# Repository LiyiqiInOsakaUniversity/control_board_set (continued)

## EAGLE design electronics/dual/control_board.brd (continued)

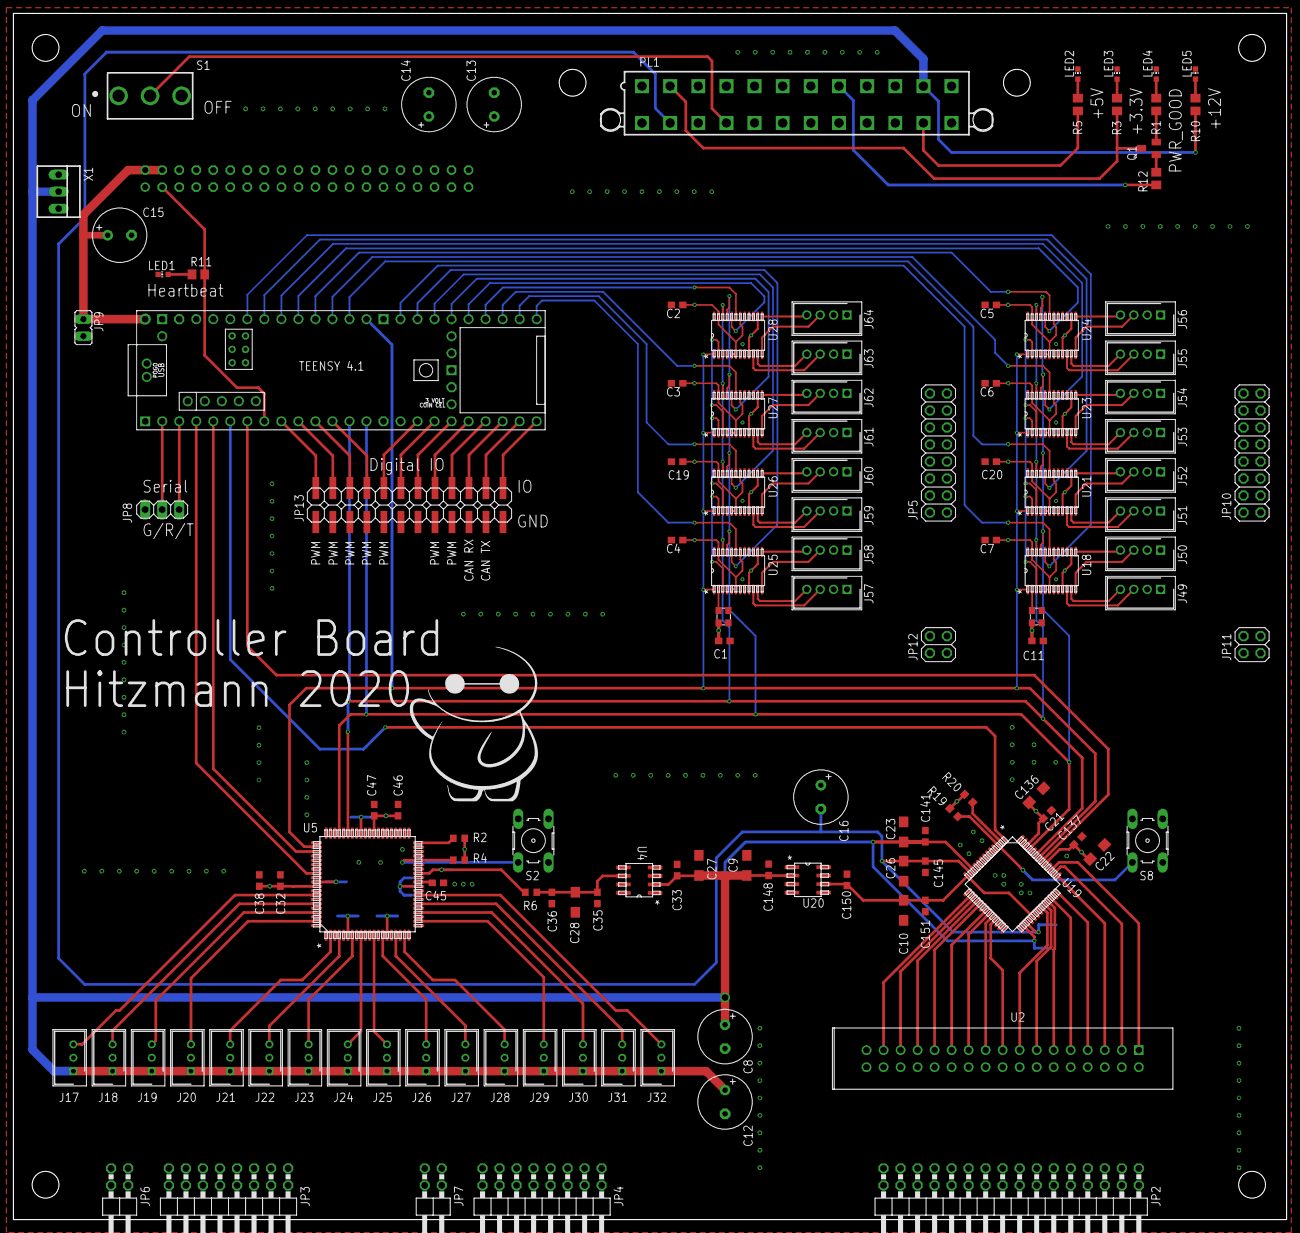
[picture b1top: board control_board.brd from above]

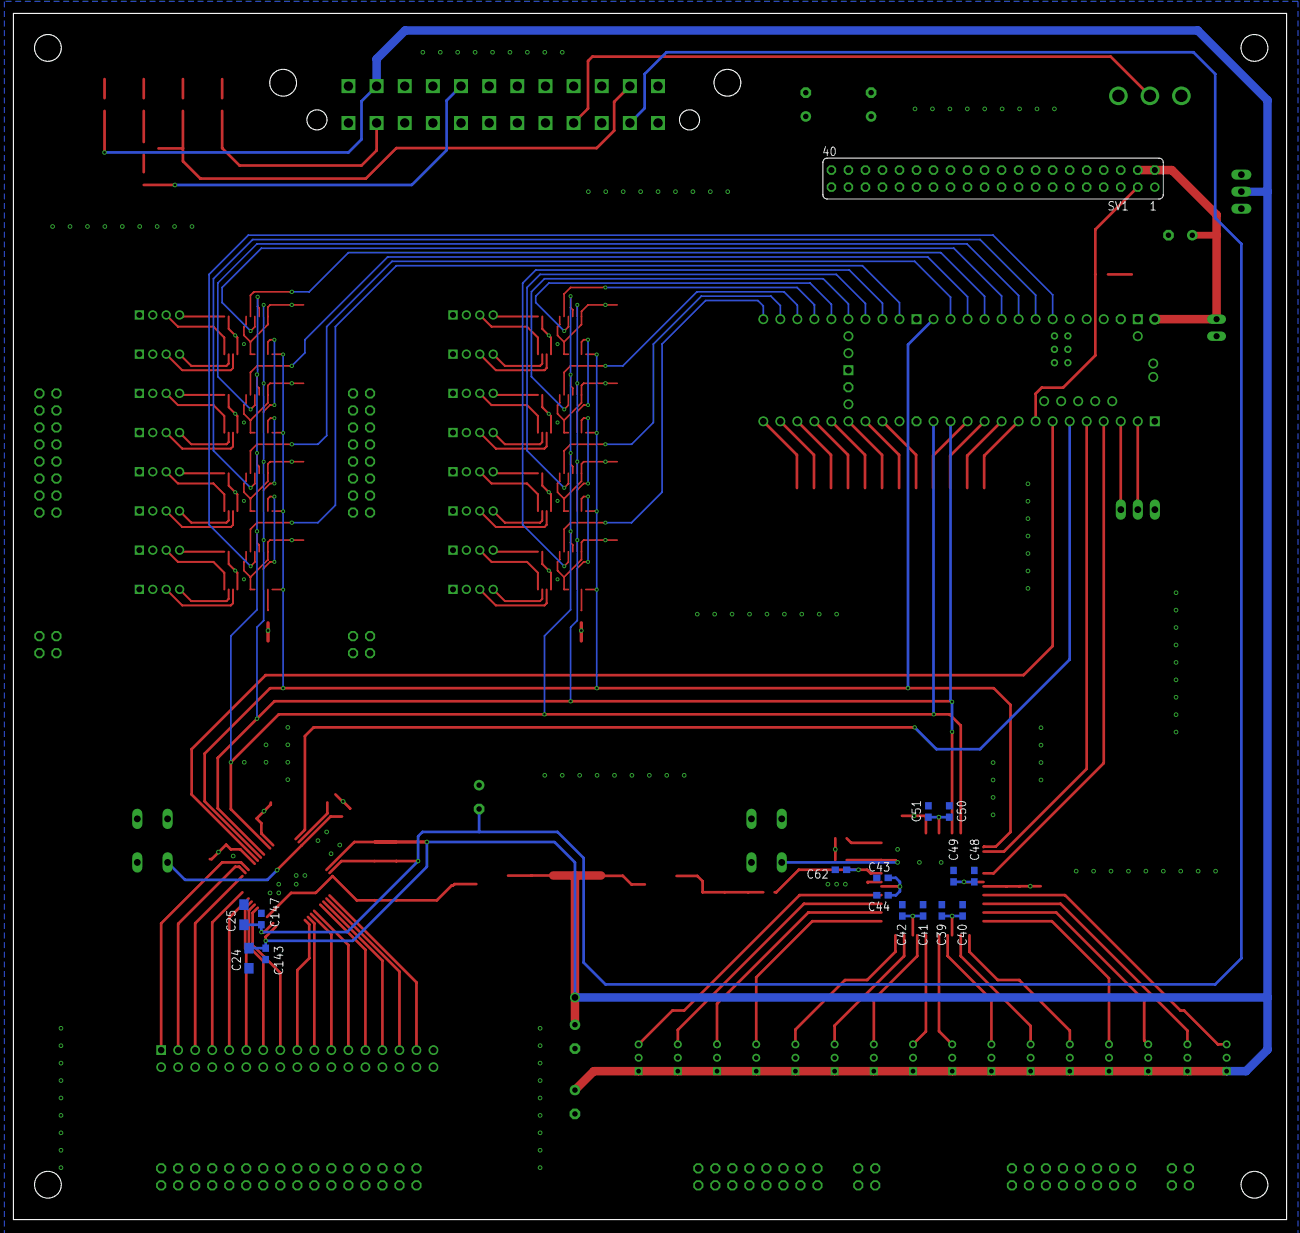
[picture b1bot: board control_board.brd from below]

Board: 4 copper layers, 190.0 x 180.0 mm, 137 parts (16 on the bottom side), 135 nets.

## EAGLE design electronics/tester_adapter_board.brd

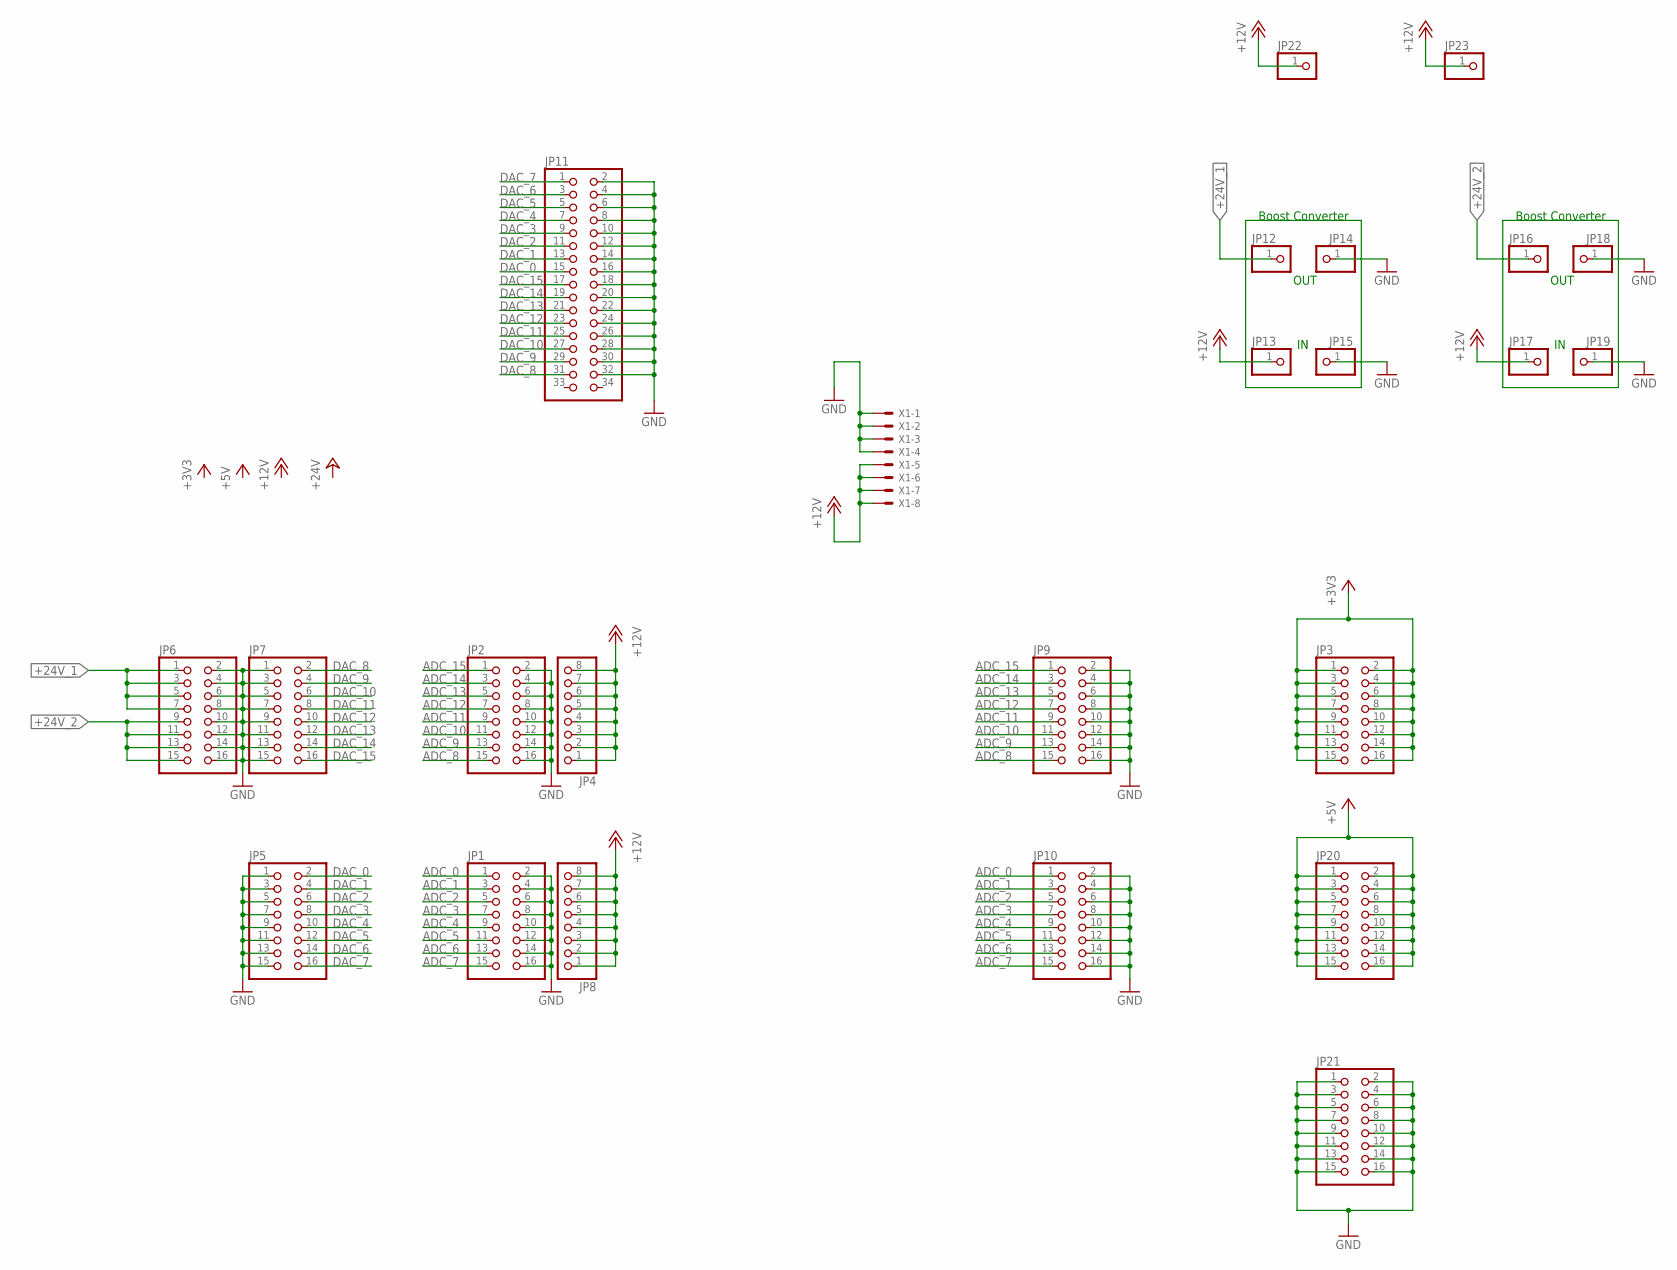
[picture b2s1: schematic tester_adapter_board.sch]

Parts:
JP1, JP2, JP3, JP5, JP6, JP7, JP9, JP10, JP20, JP21: PINHD-2X8; 2X08
JP4, JP8: PINHD-1X08_2.54-S; 1X08-S
JP11: PINHD-2X17; 2X17
JP12, JP13, JP16, JP17: PINHD-1X01_2.54; 1X01
JP14, JP15, JP18, JP19: PINHD-1X01_2.54-S; 1X01-S
JP22, JP23: PINHD-1X01_2.54-SMD; 1X01SMD
X1: 5566-8

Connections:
+3V3: JP3.1, JP3.2, JP3.3, JP3.4, JP3.5, JP3.6, JP3.7, JP3.8, JP3.9, JP3.10, JP3.11, JP3.12, JP3.13, JP3.14, JP3.15, JP3.16
+5V: JP20.1, JP20.2, JP20.3, JP20.4, JP20.5, JP20.6, JP20.7, JP20.8, JP20.9, JP20.10, JP20.11, JP20.12, JP20.13, JP20.14, JP20.15, JP20.16
+12V: JP4.1, JP4.2, JP4.3, JP4.4, JP4.5, JP4.6, JP4.7, JP4.8, JP8.1, JP8.2, JP8.3, JP8.4, JP8.5, JP8.6, JP8.7, JP8.8, JP13.1, JP17.1, JP22.1, JP23.1, X1.5, X1.6, X1.7, X1.8
+24V_1: JP6.1, JP6.3, JP6.5, JP6.7, JP12.1
+24V_2: JP6.9, JP6.11, JP6.13, JP6.15, JP16.1
ADC_0: JP1.1, JP10.1
ADC_1: JP1.3, JP10.3
ADC_2: JP1.5, JP10.5
ADC_3: JP1.7, JP10.7
ADC_4: JP1.9, JP10.9
ADC_5: JP1.11, JP10.11
ADC_6: JP1.13, JP10.13
ADC_7: JP1.15, JP10.15
ADC_8: JP2.15, JP9.15
ADC_9: JP2.13, JP9.13
ADC_10: JP2.11, JP9.11
ADC_11: JP2.9, JP9.9
ADC_12: JP2.7, JP9.7
ADC_13: JP2.5, JP9.5
ADC_14: JP2.3, JP9.3
ADC_15: JP2.1, JP9.1
DAC_0: JP5.2, JP11.15
DAC_1: JP5.4, JP11.13
DAC_2: JP5.6, JP11.11
DAC_3: JP5.8, JP11.9
DAC_4: JP5.10, JP11.7
DAC_5: JP5.12, JP11.5
DAC_6: JP5.14, JP11.3
DAC_7: JP5.16, JP11.1
DAC_8: JP7.2, JP11.31
DAC_9: JP7.4, JP11.29
DAC_10: JP7.6, JP11.27
DAC_11: JP7.8, JP11.25
DAC_12: JP7.10, JP11.23
DAC_13: JP7.12, JP11.21
DAC_14: JP7.14, JP11.19
DAC_15: JP7.16, JP11.17
GND: JP1.2, JP1.4, JP1.6, JP1.8, JP1.10, JP1.12, JP1.14, JP1.16, JP2.2, JP2.4, JP2.6, JP2.8, JP2.10, JP2.12, JP2.14, JP2.16, JP5.1, JP5.3, JP5.5, JP5.7, JP5.9, JP5.11, JP5.13, JP5.15, JP6.2, JP6.4, JP6.6, JP6.8, JP6.10, JP6.12, JP6.14, JP6.16, JP7.1, JP7.3, JP7.5, JP7.7, JP7.9, JP7.11, JP7.13, JP7.15, JP9.2, JP9.4, JP9.6, JP9.8, JP9.10, JP9.12, JP9.14, JP9.16, JP10.2, JP10.4, JP10.6, JP10.8, JP10.10, JP10.12, JP10.14, JP10.16, JP11.2, JP11.4, JP11.6, JP11.8, JP11.10, JP11.12, JP11.14, JP11.16, JP11.18, JP11.20, JP11.22, JP11.24, JP11.26, JP11.28, JP11.30, JP11.32, JP14.1, JP15.1, JP18.1, JP19.1, JP21.1, JP21.2, JP21.3, JP21.4, JP21.5, JP21.6, JP21.7, JP21.8, JP21.9, JP21.10, JP21.11, JP21.12, JP21.13, JP21.14, JP21.15, JP21.16, X1.1, X1.2, X1.3, X1.4

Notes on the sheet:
Boost Converter
OUT

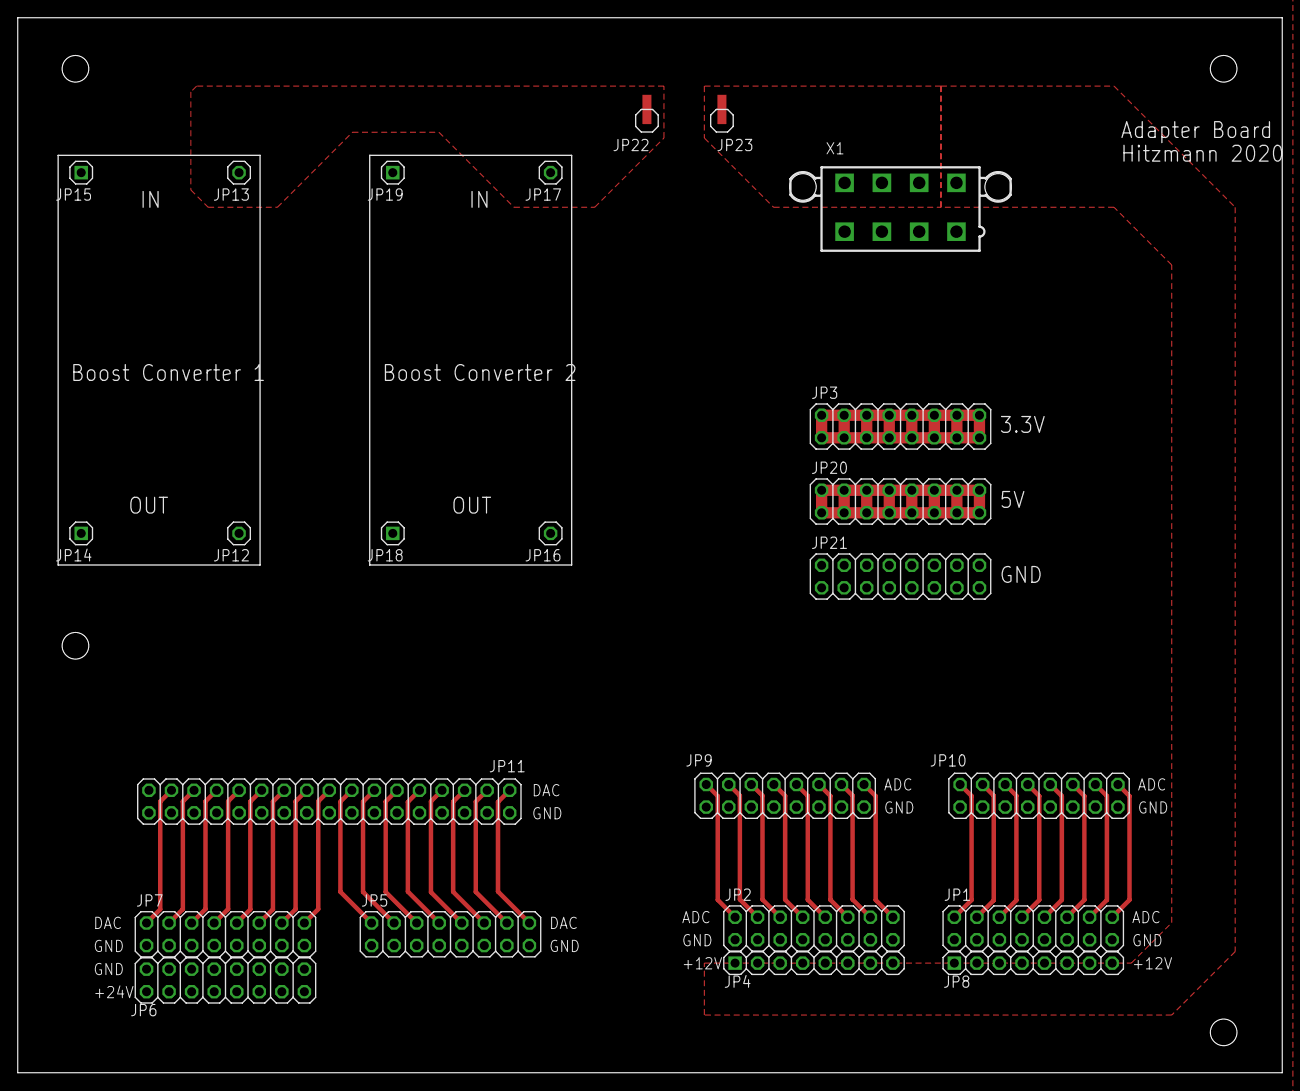
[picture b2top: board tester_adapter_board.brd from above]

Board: 2 copper layers, 142.4 x 118.8 mm, 24 parts (0 on the bottom side), 38 nets.

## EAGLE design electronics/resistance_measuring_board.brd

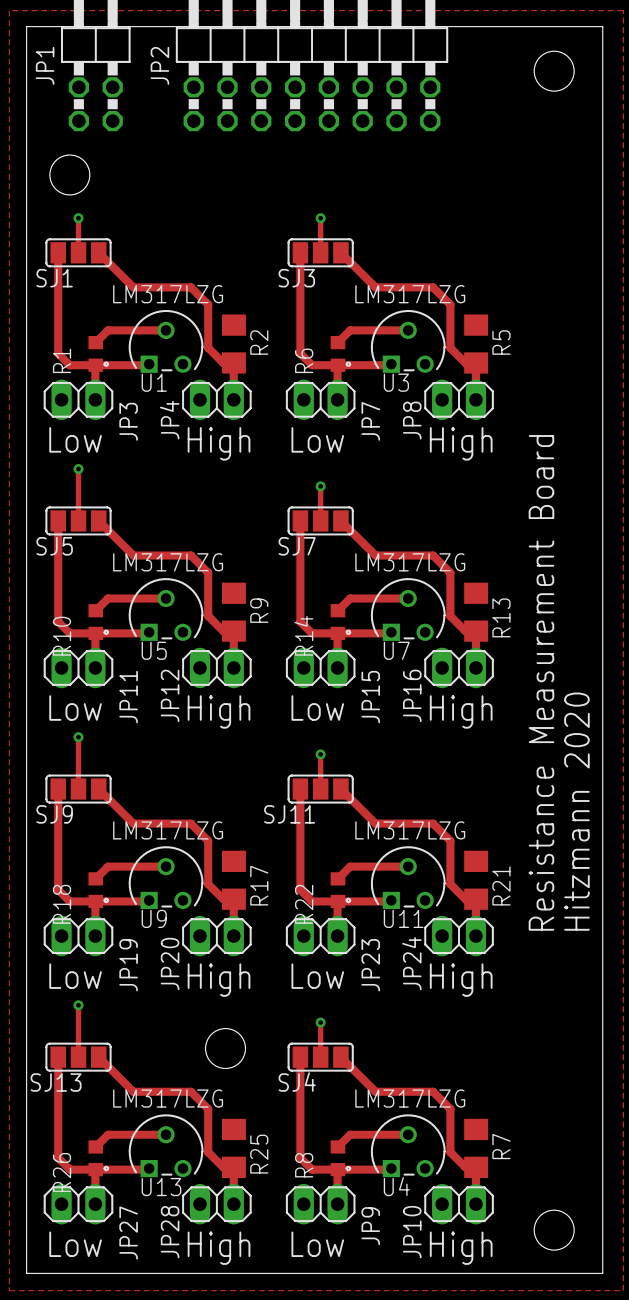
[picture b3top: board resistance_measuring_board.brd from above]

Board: 4 copper layers, 43.3 x 93.7 mm, 50 parts (0 on the bottom side), 34 nets.

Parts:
JP1: 2X02/90
JP2: 2X08/90
JP3, JP4, JP7, JP8, JP9, JP10, JP11, JP12, JP15, JP16, JP19, JP20, JP23, JP24, JP27, JP28: 1X02
R1, R6, R8, R10, R14, R18, R22, R26: 12R, 0.1%; R0603
R2, R5, R7, R9, R13, R17, R21, R25: 1K, 0.1%; R1206
SJ1, SJ3, SJ4, SJ5, SJ7, SJ9, SJ11, SJ13: SJ_2
U1, U3, U4, U5, U7, U9, U11, U13: LM317LZG; TO-92_ONS

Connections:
GND: JP2.2, JP2.4, JP2.6, JP2.8, JP2.10, JP2.12, JP2.14, JP2.16, JP3.2, JP7.2, JP9.2, JP11.2, JP15.2, JP19.2, JP23.2, JP27.2, R2.1, R5.1, R7.1, R9.1, R13.1, R17.1, R21.1, R25.1
unnamed: R6.1, U3.2
unnamed: R8.1, U4.2
unnamed: R10.1, U5.2
unnamed: R14.1, U7.2
unnamed: R18.1, U9.2
unnamed: R22.1, U11.2
unnamed: R26.1, U13.2
unnamed: R1.1, U1.2
SENSE_1: JP2.1, SJ1.2
SENSE_2: JP2.3, SJ3.2
SENSE_3: JP2.5, SJ5.2
SENSE_4: JP2.7, SJ7.2
SENSE_5: JP2.9, SJ9.2
SENSE_6: JP2.11, SJ11.2
SENSE_7: JP2.13, SJ13.2
SENSE_8: JP2.15, SJ4.2
SENSE_HI_1: JP4.2, R2.2, SJ1.1
SENSE_HI_2: JP8.2, R5.2, SJ3.1
SENSE_HI_3: JP12.2, R9.2, SJ5.1
SENSE_HI_4: JP16.2, R13.2, SJ7.1
SENSE_HI_5: JP20.2, R17.2, SJ9.1
SENSE_HI_6: JP24.2, R21.2, SJ11.1
SENSE_HI_7: JP28.2, R25.2, SJ13.1
SENSE_HI_8: JP10.2, R7.2, SJ4.1
SENSE_LO_1: JP3.1, R1.2, SJ1.3, U1.1
SENSE_LO_2: JP7.1, R6.2, SJ3.3, U3.1
SENSE_LO_3: JP11.1, R10.2, SJ5.3, U5.1
SENSE_LO_4: JP15.1, R14.2, SJ7.3, U7.1
SENSE_LO_5: JP19.1, R18.2, SJ9.3, U9.1
SENSE_LO_6: JP23.1, R22.2, SJ11.3, U11.1
SENSE_LO_7: JP27.1, R26.2, SJ13.3, U13.1
SENSE_LO_8: JP9.1, R8.2, SJ4.3, U4.1
VCC: JP1.1, JP1.2, JP1.3, JP1.4, JP4.1, JP8.1, JP10.1, JP12.1, JP16.1, JP20.1, JP24.1, JP28.1, U1.3, U3.3, U4.3, U5.3, U7.3, U9.3, U11.3, U13.3

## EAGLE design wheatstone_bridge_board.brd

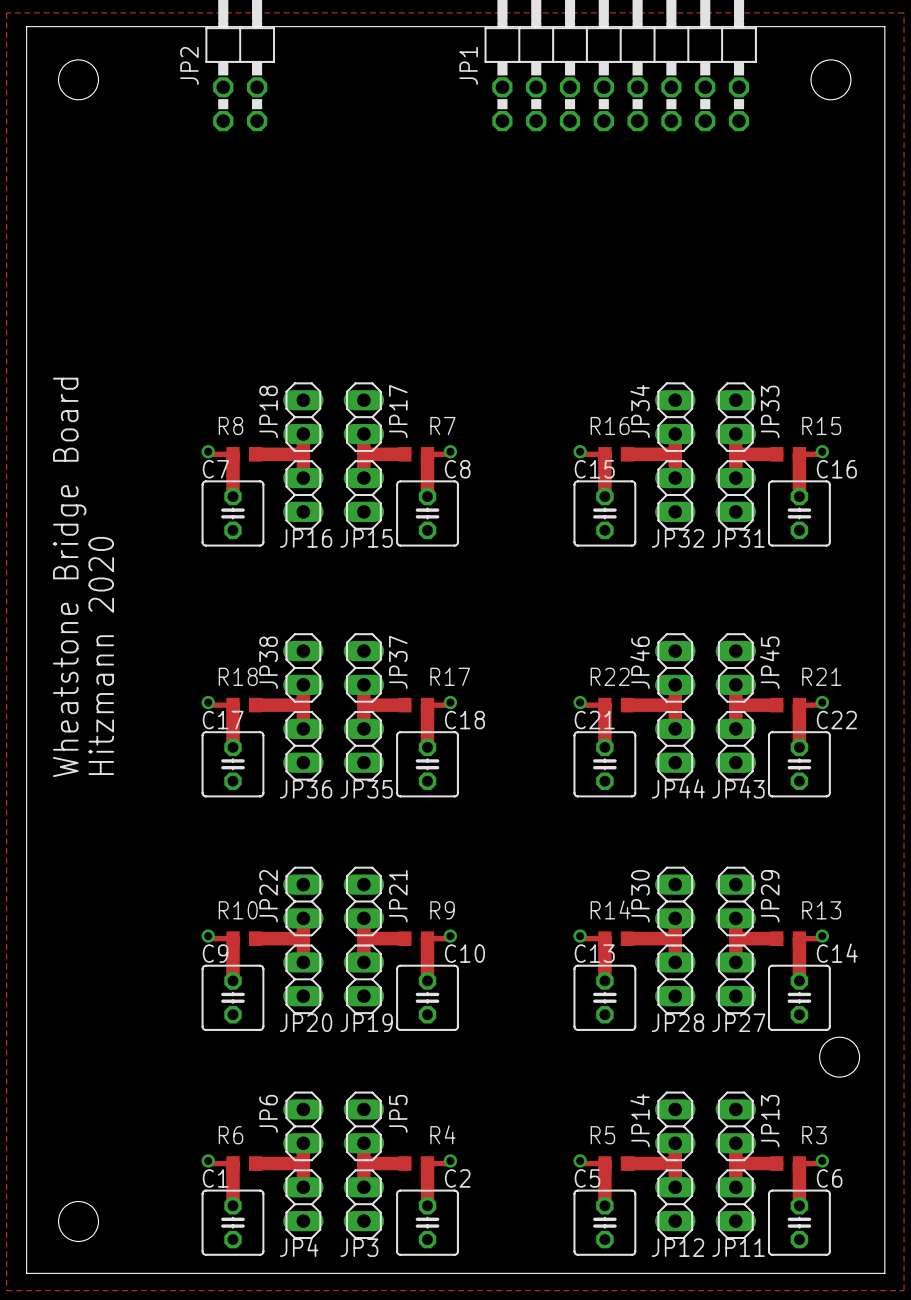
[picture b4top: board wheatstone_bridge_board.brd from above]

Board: 4 copper layers, 64.5 x 93.7 mm, 66 parts (0 on the bottom side), 34 nets.

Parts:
C1, C2, C5, C6, C7, C8, C9, C10, C13, C14, C15, C16, C17, C18, C21, C22: C025-050X050
JP1: 2X08/90
JP2: 2X02/90
JP3, JP4, JP5, JP6, JP11, JP12, JP13, JP14, JP15, JP16, JP17, JP18, JP19, JP20, JP21, JP22, JP27, JP28, JP29, JP30, JP31, JP32, JP33, JP34, JP35, JP36, JP37, JP38, JP43, JP44, JP45, JP46: 1X02
R3, R4, R5, R6, R7, R8, R9, R10, R13, R14, R15, R16, R17, R18, R21, R22: R0603

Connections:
GND: C1.2, C2.2, C5.2, C6.2, C7.2, C8.2, C9.2, C10.2, C13.2, C14.2, C15.2, C16.2, C17.2, C18.2, C21.2, C22.2, JP2.2, JP2.4, JP3.2, JP4.1, JP11.2, JP12.1, JP15.2, JP16.1, JP19.2, JP20.1, JP27.2, JP28.1, JP31.2, JP32.1, JP35.2, JP36.1, JP43.2, JP44.1
unnamed: JP4.2, JP6.1, R6.1
unnamed: JP3.1, JP5.2, R4.1
unnamed: JP12.2, JP14.1, R5.1
unnamed: JP11.1, JP13.2, R3.1
unnamed: JP16.2, JP18.1, R8.1
unnamed: JP15.1, JP17.2, R7.1
unnamed: JP20.2, JP22.1, R10.1
unnamed: JP19.1, JP21.2, R9.1
unnamed: JP28.2, JP30.1, R14.1
unnamed: JP27.1, JP29.2, R13.1
unnamed: JP32.2, JP34.1, R16.1
unnamed: JP31.1, JP33.2, R15.1
unnamed: JP36.2, JP38.1, R18.1
unnamed: JP35.1, JP37.2, R17.1
unnamed: JP44.2, JP46.1, R22.1
unnamed: JP43.1, JP45.2, R21.1
S_1_+: C2.1, JP1.1, R4.2
S_1_-: C1.1, JP1.2, R6.2
S_2_+: C6.1, JP1.9, R3.2
S_2_-: C5.1, JP1.10, R5.2
S_3_+: C10.1, JP1.3, R9.2
S_3_-: C9.1, JP1.4, R10.2
S_4_+: C14.1, JP1.11, R13.2
S_4_-: C13.1, JP1.12, R14.2
S_5_+: C18.1, JP1.5, R17.2
S_5_-: C17.1, JP1.6, R18.2
S_6_+: C22.1, JP1.13, R21.2
S_6_-: C21.1, JP1.14, R22.2
S_7_+: C8.1, JP1.7, R7.2
S_7_-: C7.1, JP1.8, R8.2
S_8_+: C16.1, JP1.15, R15.2
S_8_-: C15.1, JP1.16, R16.2
VCC: JP2.1, JP2.3, JP5.1, JP6.2, JP13.1, JP14.2, JP17.1, JP18.2, JP21.1, JP22.2, JP29.1, JP30.2, JP33.1, JP34.2, JP37.1, JP38.2, JP45.1, JP46.2

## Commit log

2020-07-30 rev 0.1
2020-07-30 added GND to Teensy
2020-07-31 added caps and logo to control board
2020-09-16 added firmware code snippets
2020-09-18 teensy test v0.0
2020-11-19 added raspi firmware
2020-12-07 working continuous mode
2020-12-08 changed load-cell datatype to uint16_t
2020-12-08 initializing all transducers
2020-12-09 fixed adc data order
2020-12-16 added deprecation notice for teensy
2020-12-22 added muscle class, changed to trailing _ for member variables
2020-12-22 added correct indices for adc and dac of muscles in muscle_test
2020-12-27 added include guard
2021-03-03 branch test- first commit by yanlin
2021-03-03 for save
2021-03-03 time span
2021-03-05 complete the file output
2021-03-05 make sure the pin
2021-03-08 change the valves
2021-03-09 muscle.cpp add get_muscle_state
2021-03-09 muscle.h add getmusclestate
2021-03-09 read data by muscle ptr
2021-03-19 tension sensor index
2021-03-19 add a new file to adjust pid
2021-03-26 new pressure list
2021-04-12 add a function for muscle spindle's resistance
2021-04-12 data
2021-04-19 static tension test
2021-04-19 add figure
2021-05-03 fixed order of adc results
2022-03-25 from yanlin
2022-03-29 2022/03/29
2022-04-04 2022/04/04
